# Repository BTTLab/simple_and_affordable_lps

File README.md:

# Simple and Affordable Linear Power Supply (0-30V, 0-3A)

This repository accompanies a video about this power supply: https://youtu.be/LigN5W8R_zc

## Disclaimer

This design is provided for educational and DIY purposes. Building a linear power supply involves potentially hazardous voltages and significant heat dissipation. Ensure that the transformer, rectifier, pass transistors, heatsinks, wiring, fusing, and enclosure are appropriately rated for your intended application.

Always take appropriate electrical safety precautions when building and testing the power supply.

This LPS is based on **Simple and Affordable Power Supply v17**: https://forum.cxem.net/topic/76820-%D0%BF%D1%80%D0%BE%D1%81%D1%82%D0%BE%D0%B9-%D0%B8-%D0%B4%D0%BE%D1%81%D1%82%D1%83%D0%BF%D0%BD%D1%8B%D0%B9-%D0%B1%D0%BF-050-%D0%B2/

My version is designed for an adjustable output voltage of **0-30 V** and an output current of **0-3 A**. However, the design can be easily adapted to achieve significantly higher output voltage and current ratings, depending on the transformer, power components, cooling, and other design considerations.

## Features

- **Constant Voltage (CV) mode** - regulates the output voltage.
- **Constant Current (CC) mode** - regulates the output current.
- **Latching overcurrent protection** - shuts down the output when an overcurrent condition occurs and remains latched until reset.
- **Overtemperature protection (OTP)** - protects the power supply against excessive temperature.
- **Transformer tap selector** - selects the appropriate transformer winding tap to improve efficiency and reduce power dissipation.
- **Four-layer PCB** - a four-layer printed circuit board designed to accommodate the circuit and its layout requirements.

## Important Note on Circuit Stability

The circuit may be prone to oscillation if inappropriate compensation capacitors are used around the operational amplifiers. The values and placement of these capacitors are important for ensuring stable operation.
Do not change the compensation capacitor values without carefully evaluating circuit stability. If modifying the design, verify its behavior under different operating conditions and loads, preferably using an oscilloscope.

## Project Files

This repository includes the KiCad project files:

- `.kicad_pro` - project configuration.
- `.kicad_sch` - schematic.
- `.kicad_pcb` - PCB layout.

and Gerber files: `Gerber.zip`
The PCB is 150 x 100 mm, 4 layers, THT + SMD components.

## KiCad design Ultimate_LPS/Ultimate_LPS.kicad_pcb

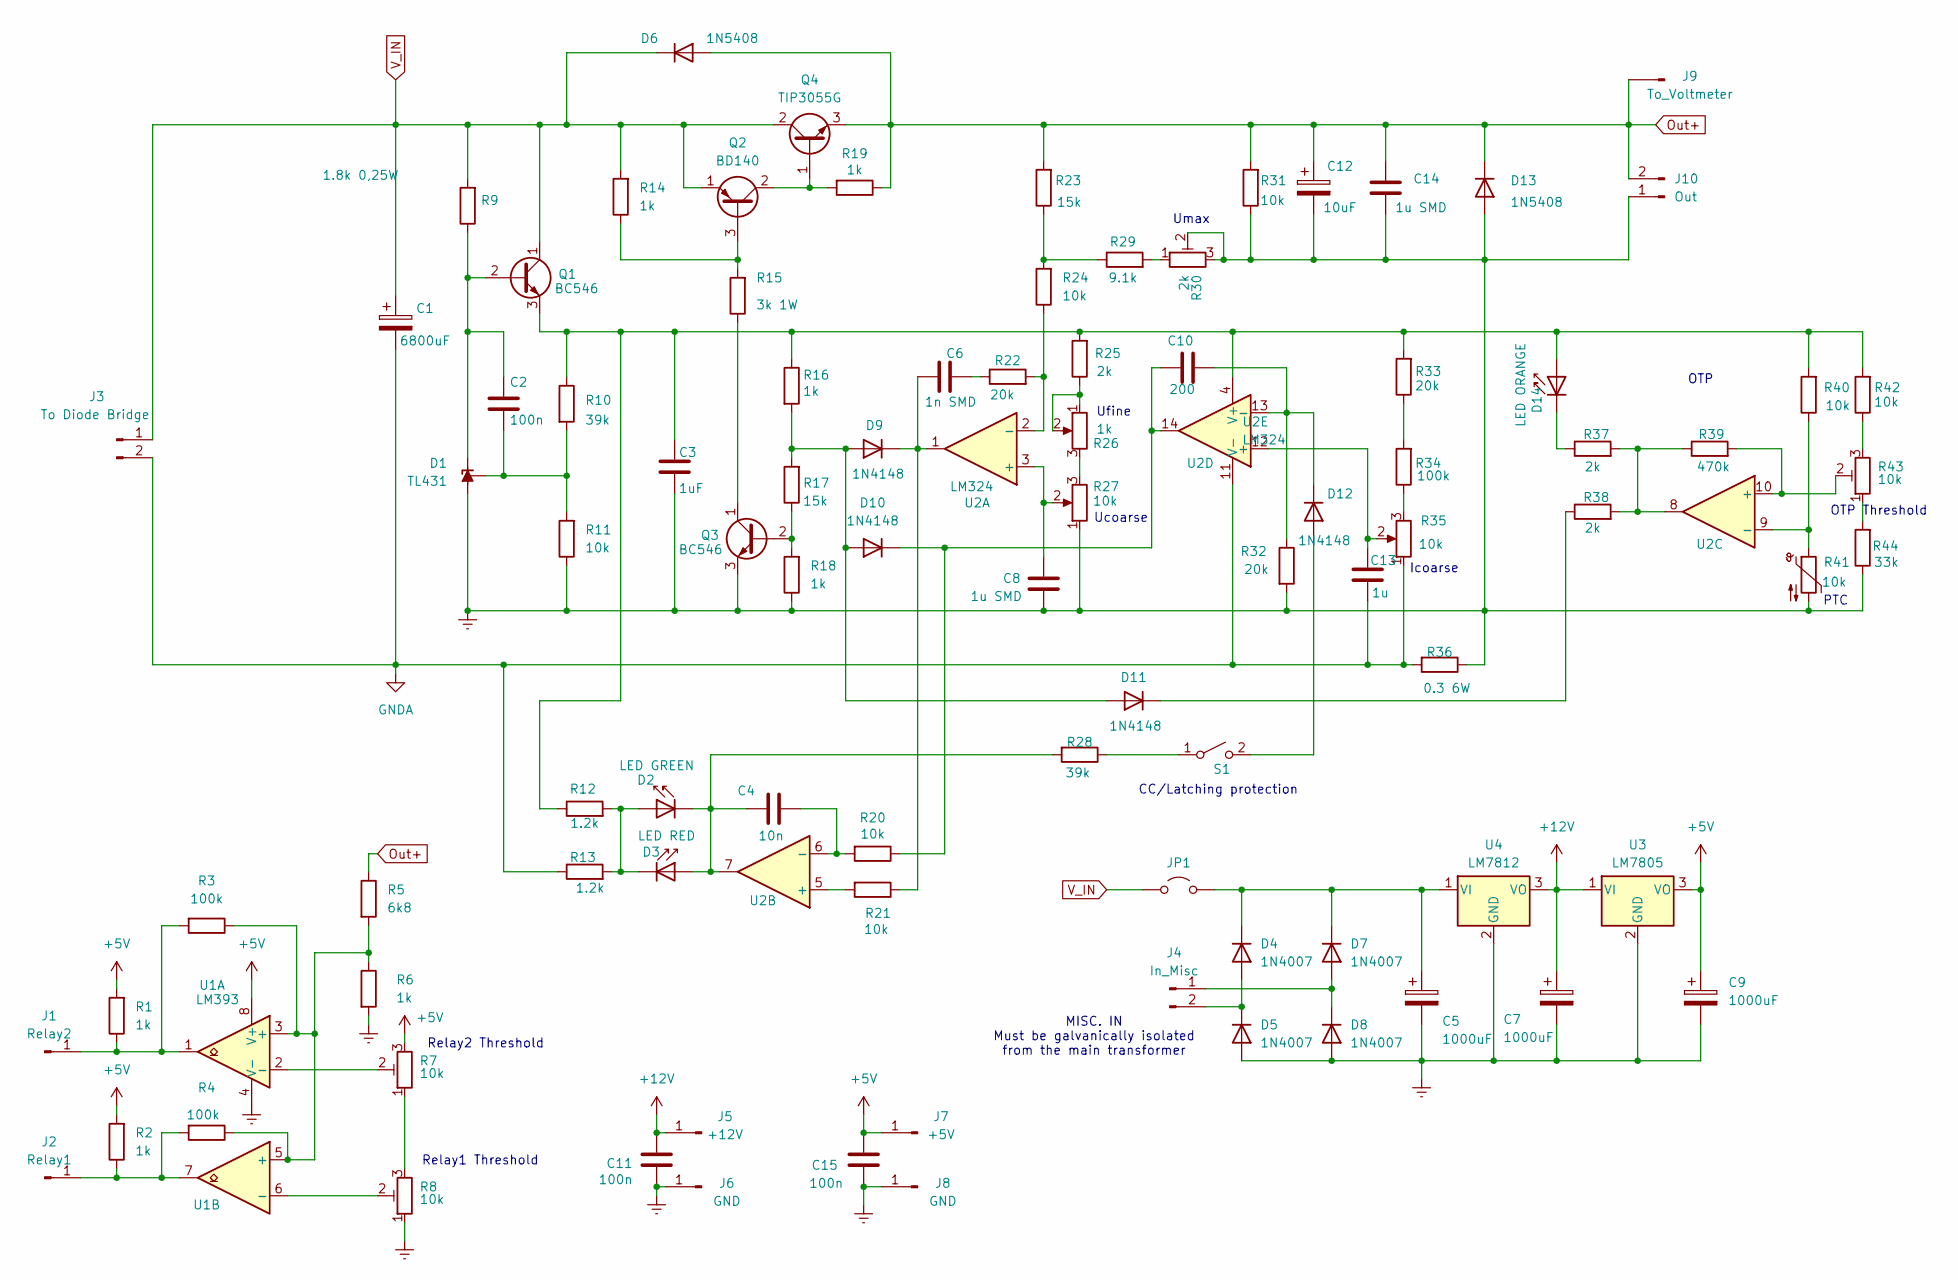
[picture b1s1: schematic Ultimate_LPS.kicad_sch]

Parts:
C1: 6800uF; CP_Radial_D35.0mm_P10.00mm_SnapIn
C2: 100n; C_Rect_L13.0mm_W5.0mm_P10.00mm_FKS3_FKP3_MKS4
C3: 1uF; C_1206_3216Metric_Pad1.33x1.80mm_HandSolder
C4: 10n; C_Rect_L13.0mm_W5.0mm_P10.00mm_FKS3_FKP3_MKS4
C5, C7, C9: 1000uF; CP_Radial_D10.0mm_P5.00mm
C6: 1n SMD; C_0603_1608Metric_Pad1.08x0.95mm_HandSolder
C8, C14: 1u SMD; C_1206_3216Metric_Pad1.33x1.80mm_HandSolder
C10: 200; C_Rect_L7.0mm_W2.5mm_P5.00mm
C11, C15: 100n; C_0603_1608Metric_Pad1.08x0.95mm_HandSolder
C12: 10uF; CP_Radial_D5.0mm_P2.00mm
C13: 1u; C_Rect_L13.0mm_W5.0mm_P10.00mm_FKS3_FKP3_MKS4
D1: TL431; TO-92_Inline
D2: LED GREEN; LED_D3.0mm_IRBlack
D3: LED RED; LED_D3.0mm_IRBlack
D4, D5, D7, D8: 1N4007; D_DO-41_SOD81_P10.16mm_Horizontal
D6, D13: 1N5408; D_DO-201AD_P15.24mm_Horizontal
D9, D10, D11, D12: 1N4148; D_DO-35_SOD27_P7.62mm_Horizontal
D14: LED ORANGE; LED_D3.0mm_IRBlack
J1: Relay2; Pin_D1.0mm_L10.0mm
J2: Relay1; Pin_D1.0mm_L10.0mm
J3: To Diode Bridge; SolderWire-1sqmm_1x02_P5.4mm_D1.4mm_OD2.7mm
J4: In_Misc; SolderWire-1sqmm_1x02_P5.4mm_D1.4mm_OD2.7mm
J5: +12V; Pin_D1.0mm_L10.0mm
J6, J8: GND; Pin_D1.0mm_L10.0mm
J7: +5V; Pin_D1.0mm_L10.0mm
J9: To_Voltmeter; Pin_D1.0mm_L10.0mm
J10: Out; SolderWire-1sqmm_1x02_P5.4mm_D1.4mm_OD2.7mm
JP1: Jumper; R_Axial_DIN0204_L3.6mm_D1.6mm_P2.54mm_Vertical
Q1, Q3: BC546; TO-92_Inline
Q2: BD140; TO-126-3_Vertical
Q4: TIP3055G; TO-247-3_Vertical
R1, R2, R6, R14, R16, R18: 1k; R_Axial_DIN0207_L6.3mm_D2.5mm_P15.24mm_Horizontal
R3, R4, R34: 100k; R_Axial_DIN0207_L6.3mm_D2.5mm_P15.24mm_Horizontal
R5: 6k8; R_Axial_DIN0207_L6.3mm_D2.5mm_P15.24mm_Horizontal
R7, R8, R43: 10k; Potentiometer_Bourns_3296W_Vertical
R9: 1.8k 0,25W; R_Axial_DIN0207_L6.3mm_D2.5mm_P15.24mm_Horizontal
R10, R28: 39k; R_Axial_DIN0207_L6.3mm_D2.5mm_P15.24mm_Horizontal
R11, R20, R21, R24, R31, R42: 10k; R_Axial_DIN0207_L6.3mm_D2.5mm_P15.24mm_Horizontal
R12, R13: 1.2k; R_Axial_DIN0207_L6.3mm_D2.5mm_P15.24mm_Horizontal
R15: 3k 1W; R_Axial_DIN0309_L9.0mm_D3.2mm_P15.24mm_Horizontal
R17, R23: 15k; R_Axial_DIN0207_L6.3mm_D2.5mm_P15.24mm_Horizontal
R19: 1k; R_Axial_DIN0207_L6.3mm_D2.5mm_P10.16mm_Horizontal
R22, R32, R33: 20k; R_Axial_DIN0207_L6.3mm_D2.5mm_P15.24mm_Horizontal
R25, R37, R38: 2k; R_Axial_DIN0207_L6.3mm_D2.5mm_P15.24mm_Horizontal
R26: 1k; Potentiometer_Piher_PC-16_Single_Horizontal
R27, R35: 10k; Potentiometer_Piher_PC-16_Single_Horizontal
R29: 9.1k; R_Axial_DIN0207_L6.3mm_D2.5mm_P15.24mm_Horizontal
R30: 2k; Potentiometer_Bourns_3296W_Vertical
R36: 0.3 6W; R_Axial_Power_L25.0mm_W9.0mm_P27.94mm
R39: 470k; R_Axial_DIN0207_L6.3mm_D2.5mm_P15.24mm_Horizontal
R40: 10k; R_1206_3216Metric_Pad1.30x1.75mm_HandSolder
R41: 10k; PinHeader_1x02_P2.54mm_Vertical
R44: 33k; R_Axial_DIN0207_L6.3mm_D2.5mm_P15.24mm_Horizontal
S1: PinHeader_1x02_P2.54mm_Vertical
U1: LM393; DIP-8_W7.62mm_LongPads
U2: LM324; DIP-14_W7.62mm_LongPads
U3: LM7805; TO-220-3_Vertical
U4: LM7812; TO-220-3_Vertical

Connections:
+5V: C9.1, C15.2, J7.1, R1.2, R2.2, R7.3, U1.8 (V+), U3.3 (VO)
+12V: C7.1, C11.2, J5.1, U3.1 (VI), U4.3 (VO)
Earth: C3.2, C5.2, C7.2, C8.2, C9.2, C11.1, C12.2, C14.2, C15.1, D1.2 (A), D5.2 (A), D8.2 (A), D13.2 (A), J6.1, J8.1, J10.1, Q3.3 (E), R6.2, R8.1, R11.1, R18.1, R27.1, R30.2, R30.3, R31.1, R32.2, R36.1, R41.2, R44.1, U1.4 (V-), U3.2 (GND), U4.2 (GND)
GNDA: C1.2, C13.2, J3.2, R13.1, R35.1, R36.2, U2.11 (V-)
unnamed: C6.2, R22.1
unnamed: C2.1, D1.3 (K), Q1.2 (B), R9.1
unnamed: C2.2, D1.1 (REF), R10.2, R11.2
unnamed: D2.2 (A), D3.1 (K), R12.2, R13.2
unnamed: C4.1, D2.1 (K), D3.2 (A), R28.2, U2.7
unnamed: D4.2 (A), D5.1 (K), J4.2
unnamed: C5.1, D4.1 (K), D7.1 (K), JP1.2 (B), U4.1 (VI)
unnamed: D7.2 (A), D8.1 (K), J4.1
unnamed: C6.1, D9.1 (K), R21.1, U2.1
unnamed: D9.2 (A), D10.2 (A), D11.2 (A), R16.2, R17.2
unnamed: C10.1, D10.1 (K), R20.1, U2.14
unnamed: D11.1 (K), R38.1
unnamed: D12.2 (A), S1.2 (B)
unnamed: C10.2, D12.1 (K), R32.1, U2.13 (-)
unnamed: C3.1, D14.2 (A), Q1.3 (E), R10.1, R12.1, R16.1, R25.2, R33.2, R40.2, R42.2, U2.4 (V+)
unnamed: D14.1 (K), R37.1
unnamed 20: J1.1, R1.1, R3.2, U1.1; also elsewhere on the board
unnamed 21: J2.1, R2.1, R4.2, U1.7; also elsewhere on the board
unnamed: Q2.3 (B), R14.1, R15.2
unnamed: Q2.2 (C), Q4.1 (B), R19.2
unnamed: Q3.2 (B), R17.1, R18.2
unnamed: Q3.1 (C), R15.1
unnamed: R7.1, R8.3
unnamed: R23.1, R24.2, R29.1
unnamed: R25.1, R26.1, R26.2
unnamed: R26.3, R27.3
unnamed: R29.2, R30.1
unnamed: R33.1, R34.2
unnamed: R34.1, R35.3
unnamed: R37.2, R38.2, R39.1, U2.8
unnamed: R42.1, R43.3
unnamed: R43.1, R44.2
unnamed: R28.1, S1.1 (A)
unnamed: R3.1, R4.1, R5.2, R6.1, U1.3 (+), U1.5 (+)
unnamed: R7.2, U1.2 (-)
unnamed: R8.2, U1.6 (-)
unnamed: C8.1, R27.2, U2.3 (+)
unnamed: R22.2, R24.1, U2.2 (-)
unnamed: R21.2, U2.5 (+)
unnamed: C4.2, R20.2, U2.6 (-)
unnamed: R39.2, R43.2, U2.10 (+)
unnamed: R40.1, R41.1, U2.9 (-)
unnamed: C13.1, R35.2, U2.12 (+)
Out+: C12.1, C14.1, D6.2 (A), D13.1 (K), J9.1, J10.2, Q4.3 (E), R5.1, R19.1, R23.2, R31.2
V_IN: C1.1, D6.1 (K), J3.1, JP1.1 (A), Q1.1 (C), Q2.1 (E), Q4.2 (C), R9.2, R14.2

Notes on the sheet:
MISC. IN Must be galvanically isolated from the main transformer
CC/Latching protection
Ufine
Relay1 Threshold
Icoarse
Ucoarse
OTP
Relay2 Threshold
PTC
OTP Threshold
Umax

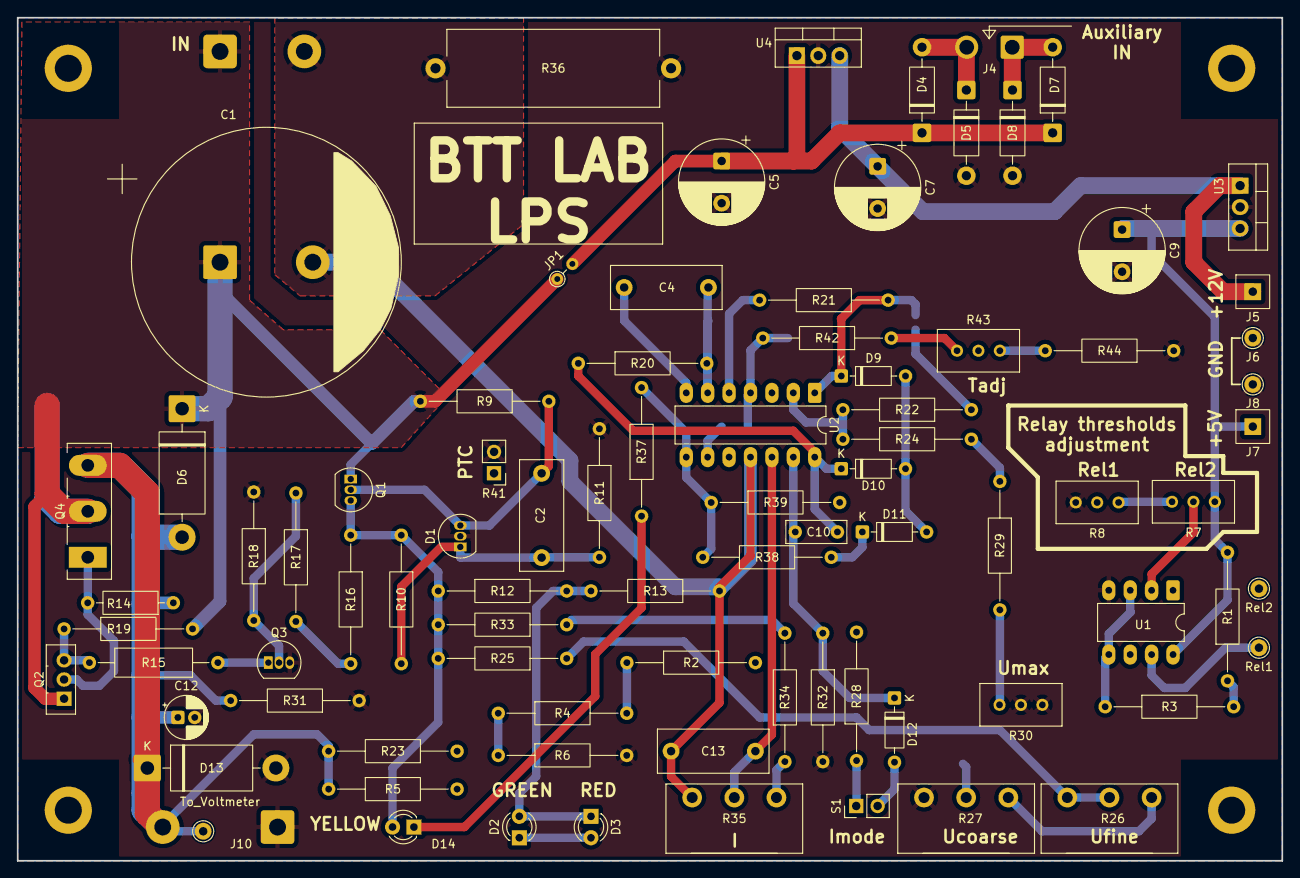
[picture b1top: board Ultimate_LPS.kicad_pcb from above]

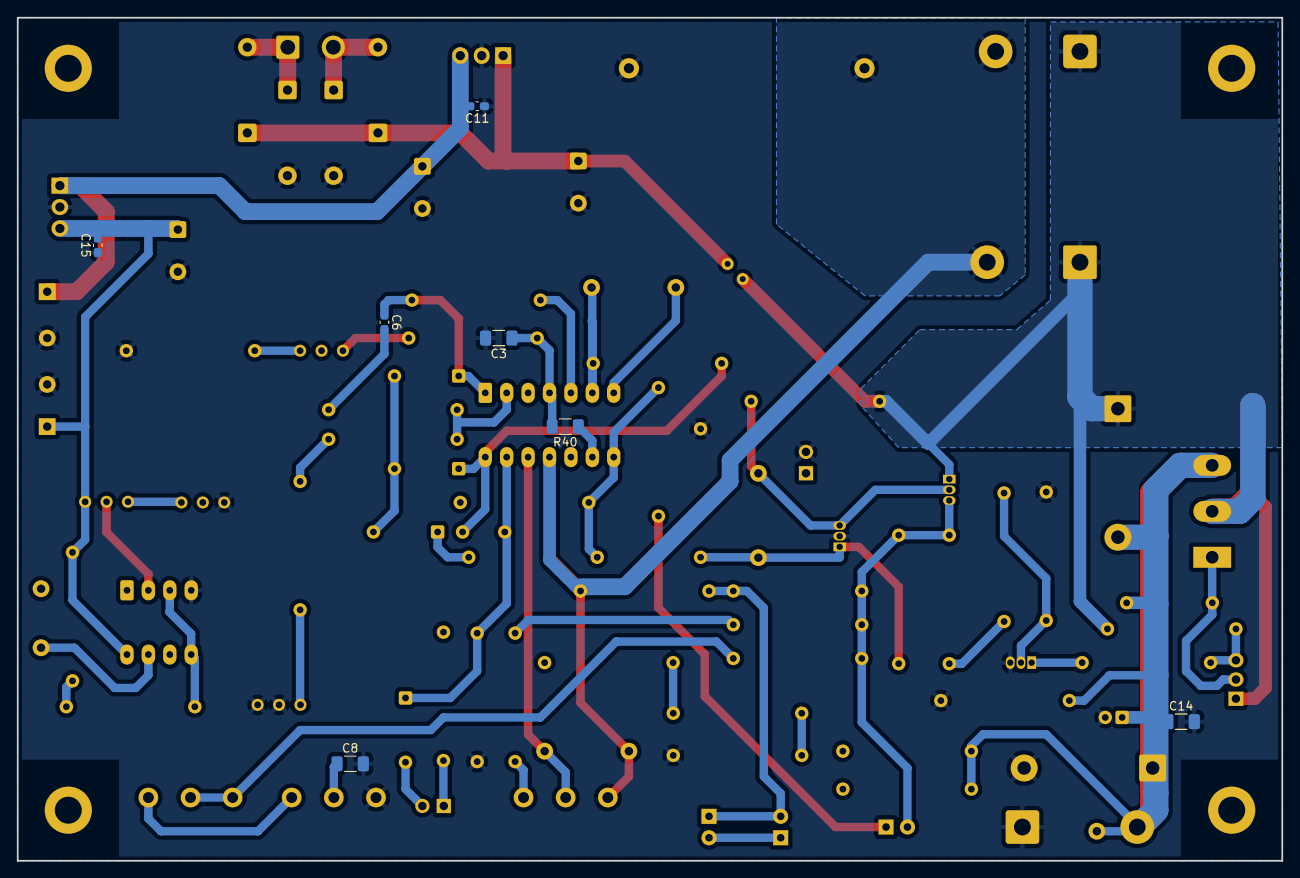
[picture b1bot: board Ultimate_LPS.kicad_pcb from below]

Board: 4 copper layers, 150.0 x 100.0 mm, 93 parts (7 on the bottom side), 49 nets.

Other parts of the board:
Rel1: Relay1; Pin_D1.0mm_L10.0mm
Rel2: Relay2; Pin_D1.0mm_L10.0mm

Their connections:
unnamed 20: Rel2.1; also elsewhere on the board
unnamed 21: Rel1.1; also elsewhere on the board
